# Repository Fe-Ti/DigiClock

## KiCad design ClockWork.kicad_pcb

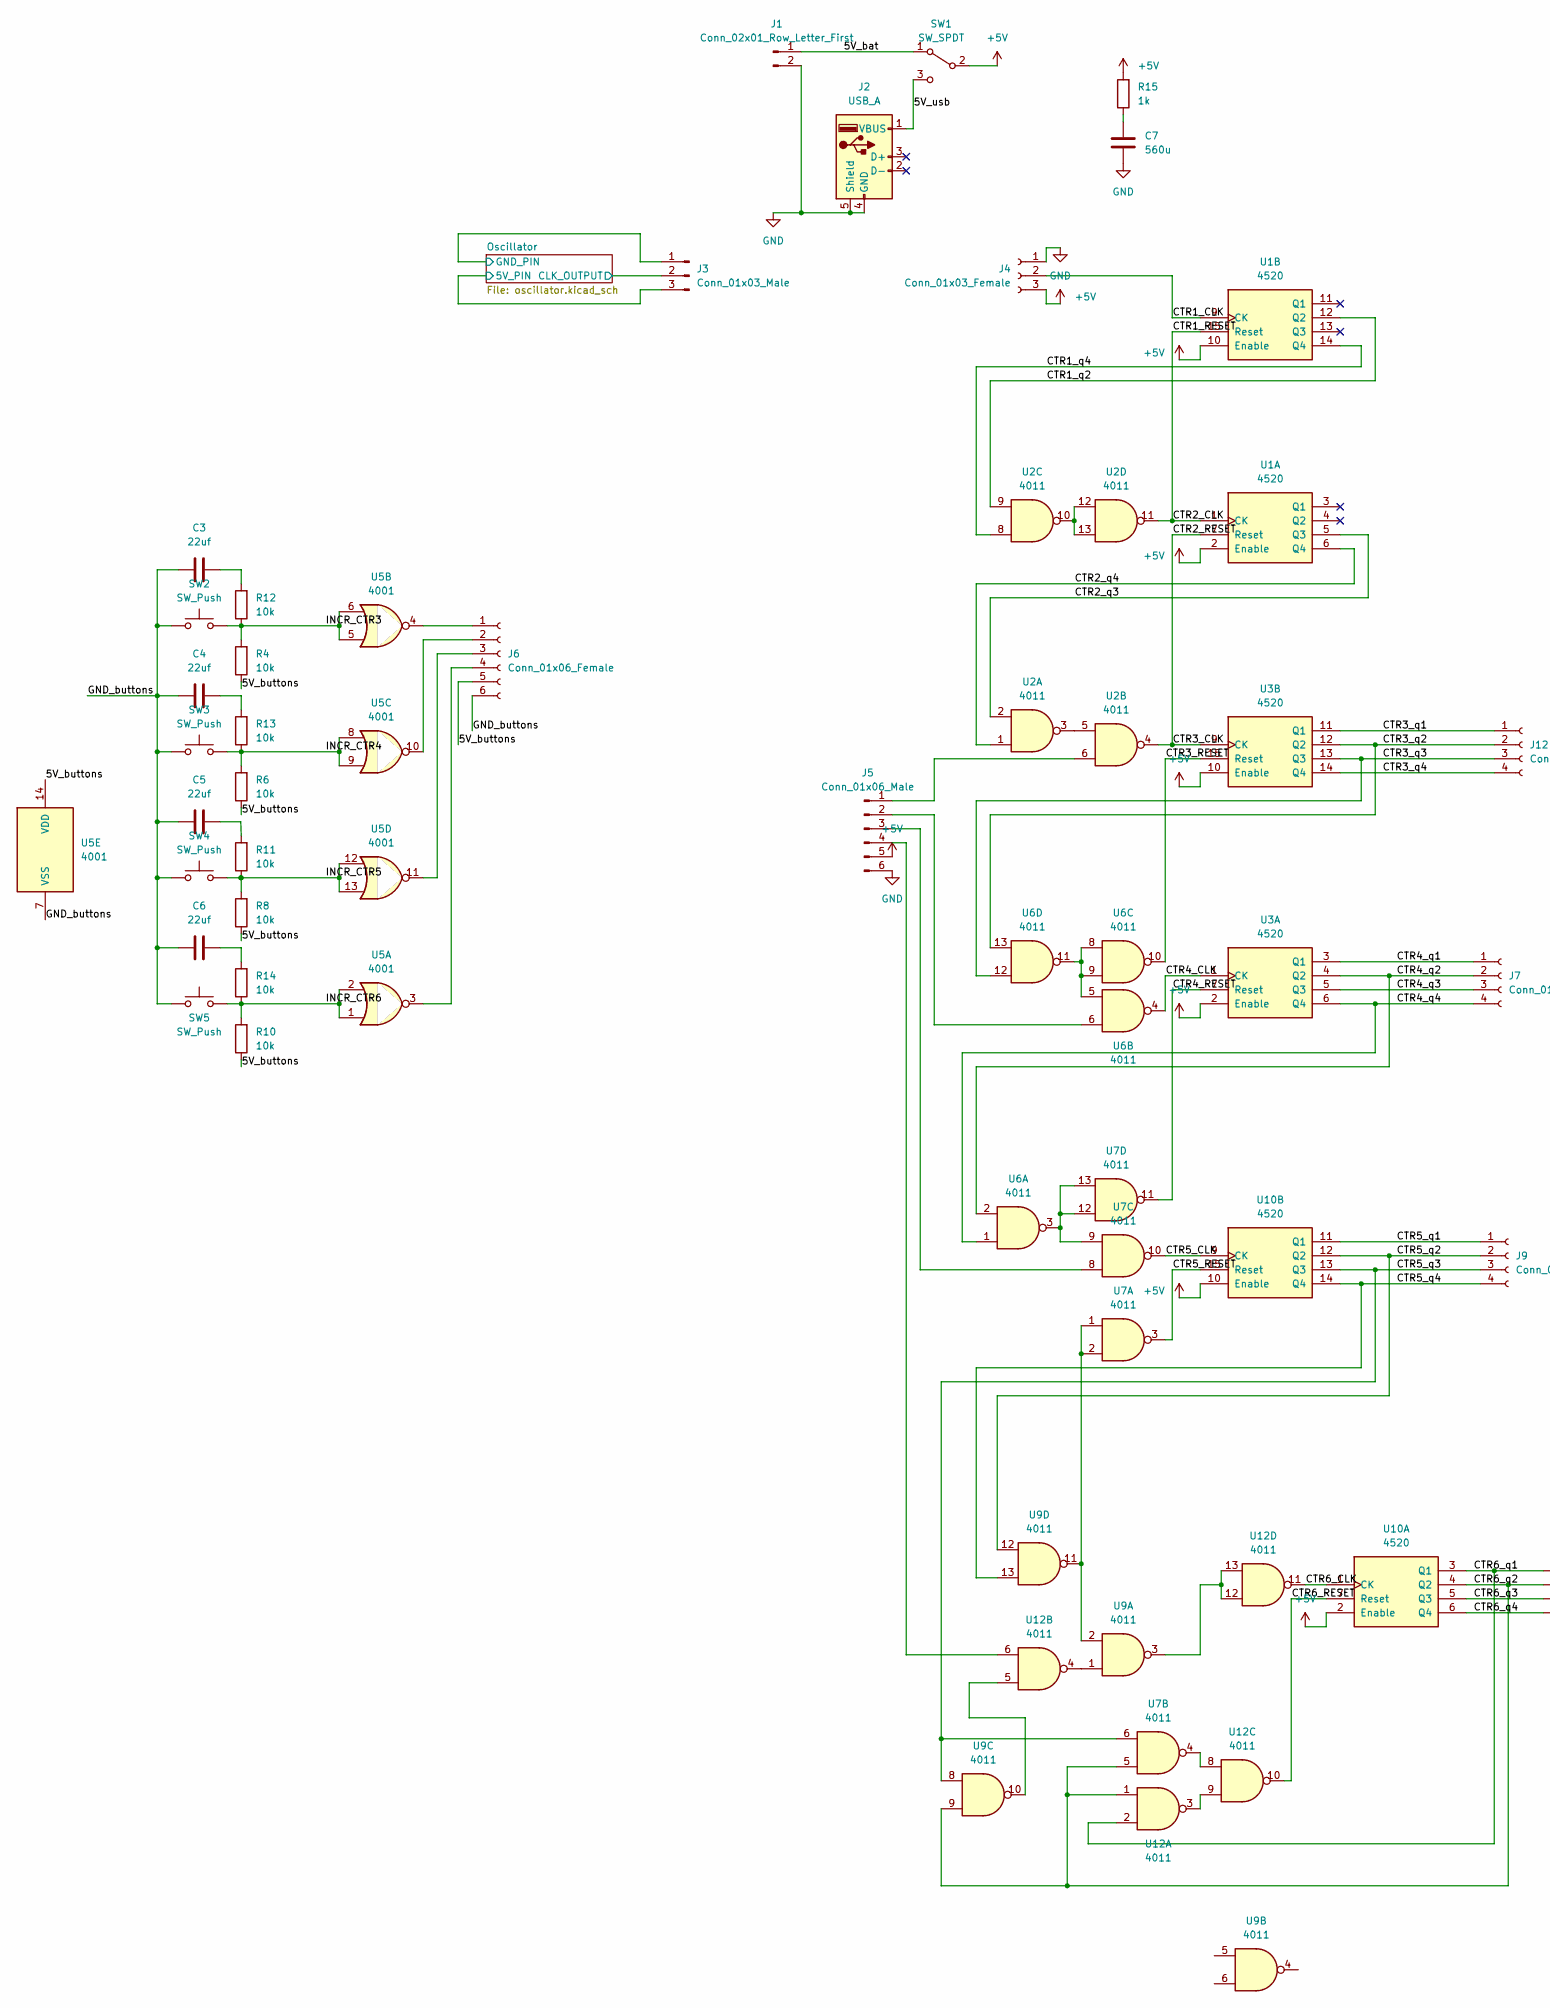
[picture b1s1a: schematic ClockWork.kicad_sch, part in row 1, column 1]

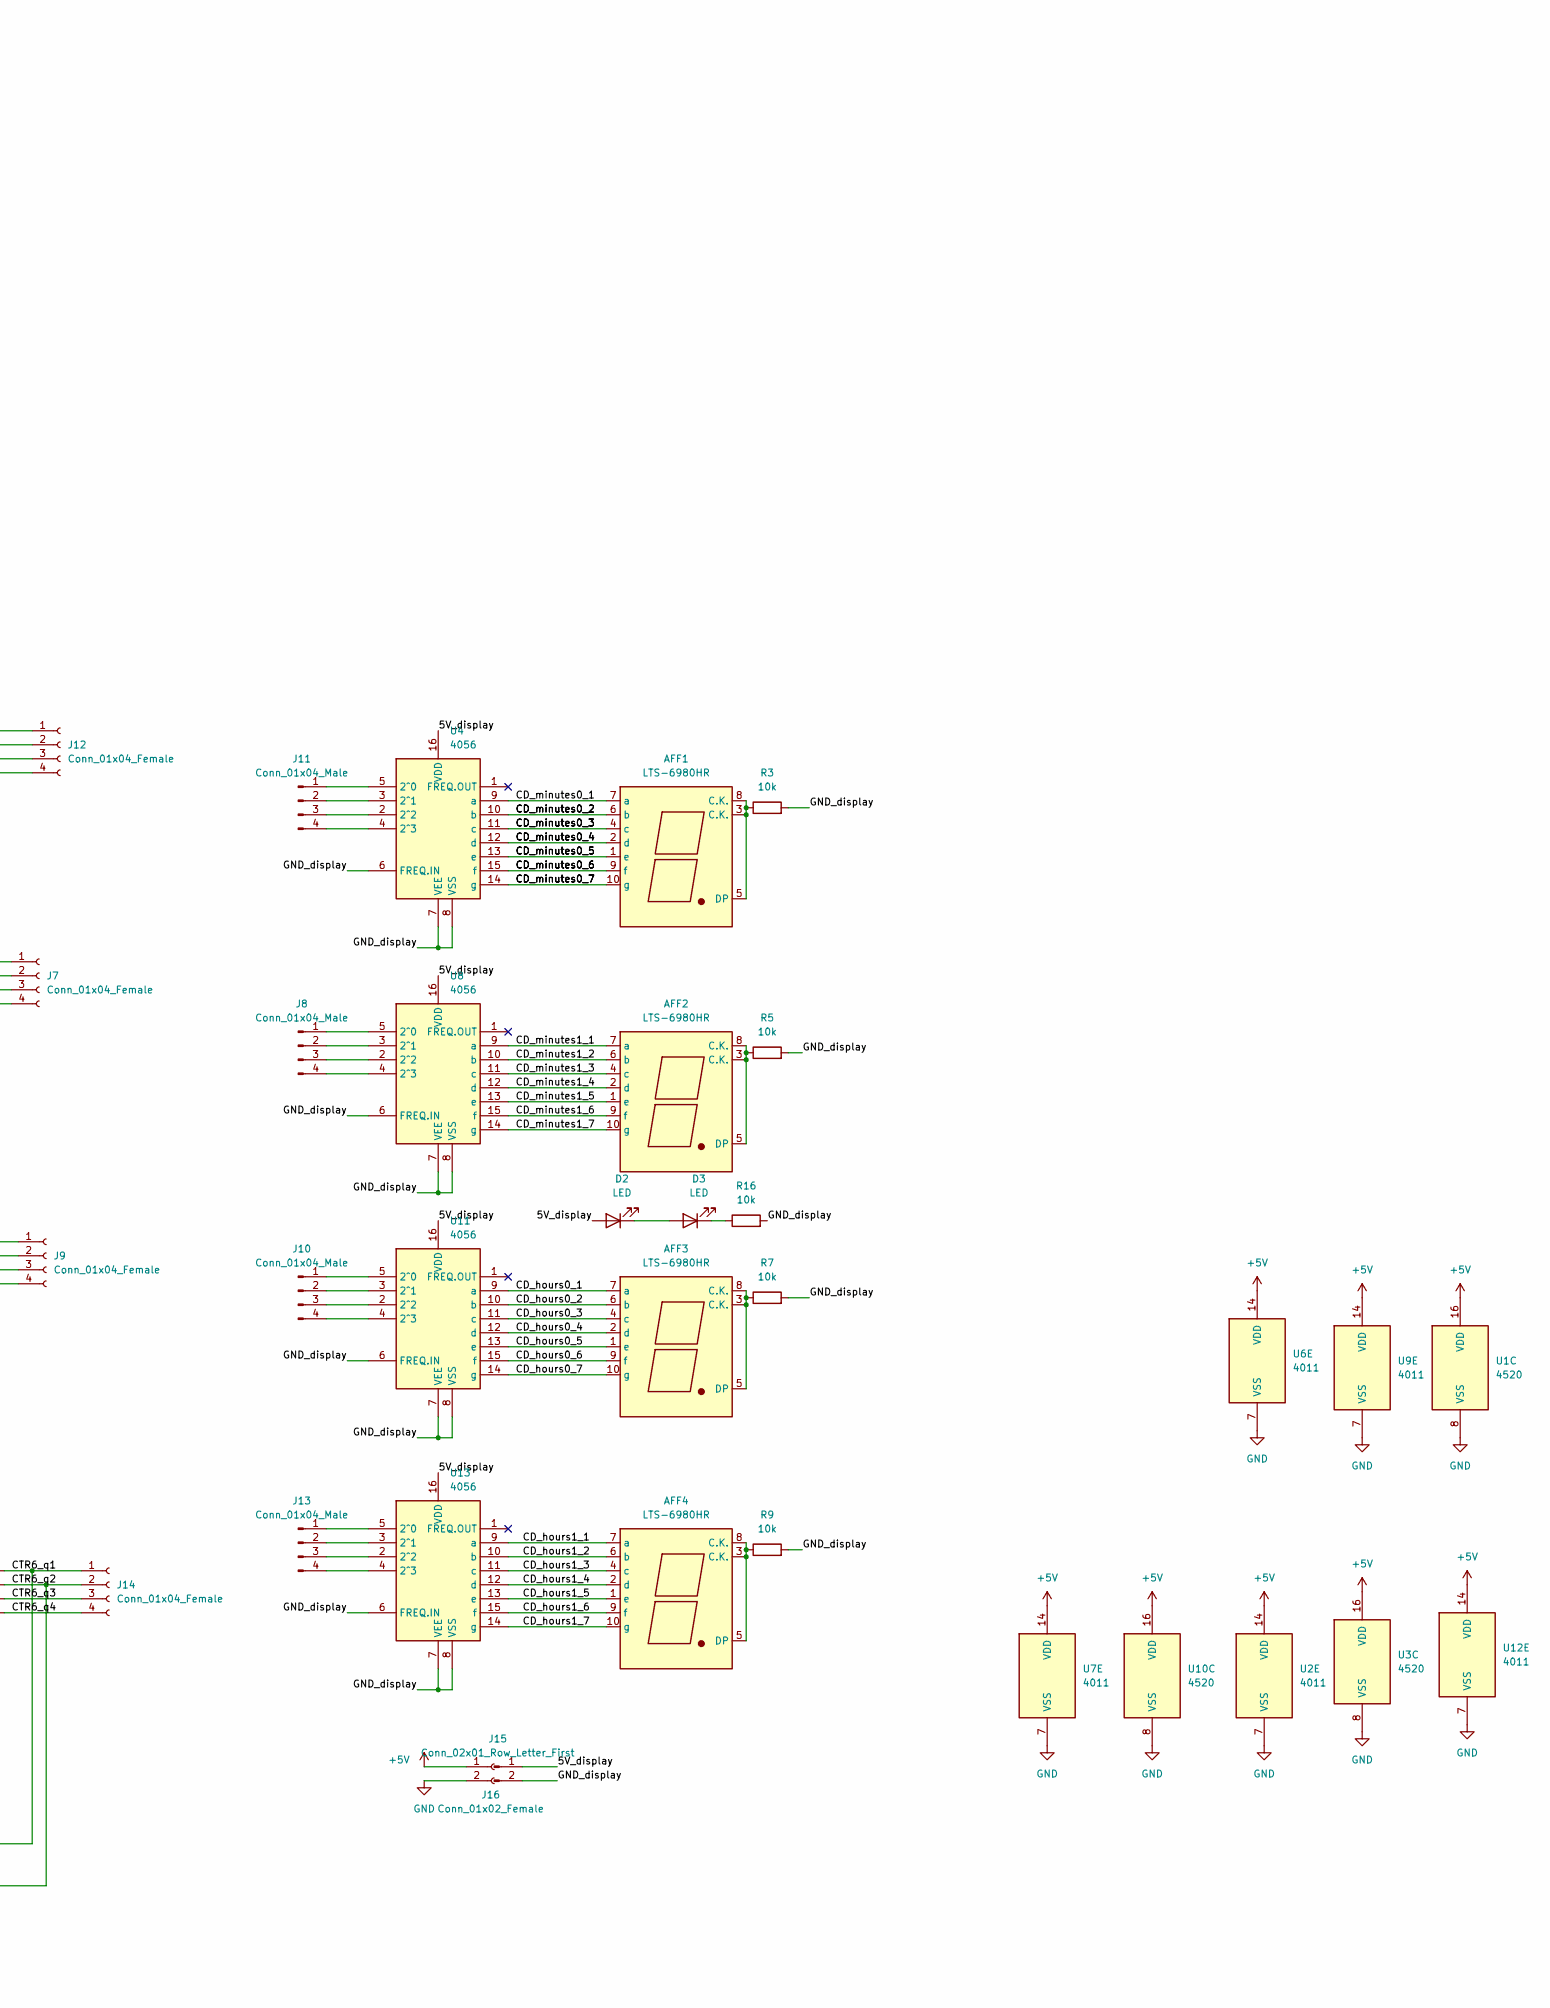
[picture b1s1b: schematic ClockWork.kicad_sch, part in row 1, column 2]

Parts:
AFF1, AFF2, AFF3, AFF4: LTS-6980HR; 7SegmentLED_LTS6760_LTS6780
C3, C4, C5, C6: 22uf; CP_Axial_L10.0mm_D4.5mm_P15.00mm_Horizontal
C7: 560u; CP_Radial_D10.0mm_P5.00mm
D2, D3: LED; LED_D5.0mm
J1: Conn_02x01_Row_Letter_First; PinHeader_1x02_P2.54mm_Vertical
J2: USB_A; USB_A_CONNFLY_DS1095-WNR0
J3: Conn_01x03_Male; PinHeader_1x03_P2.54mm_Vertical
J4: Conn_01x03_Female; PinSocket_1x03_P2.54mm_Vertical
J5: Conn_01x06_Male; PinSocket_1x06_P2.54mm_Vertical
J6: Conn_01x06_Female; PinSocket_1x06_P2.54mm_Vertical
J7, J9, J12, J14: Conn_01x04_Female; PinSocket_1x04_P2.54mm_Vertical
J8, J10, J11, J13: Conn_01x04_Male; PinSocket_1x04_P2.54mm_Vertical
J15: Conn_02x01_Row_Letter_First; PinSocket_1x02_P2.54mm_Vertical
J16: Conn_01x02_Female; PinSocket_1x02_P2.54mm_Vertical
R3, R4, R5, R6, R7, R8, R9, R10, R11, R12, R13, R14, R16: 10k; R_Axial_DIN0207_L6.3mm_D2.5mm_P7.62mm_Horizontal
R15: 1k; R_Axial_DIN0207_L6.3mm_D2.5mm_P7.62mm_Horizontal
SW1: SW_SPDT; PinSocket_1x03_P2.54mm_Vertical
SW2, SW3, SW4, SW5: SW_Push; SW_SPST_B3S-1000
U1, U3, U10: 4520; DIP-16_W7.62mm_Socket
U2, U6, U7, U9, U12: 4011; DIP-14_W7.62mm_Socket
U4, U8, U11, U13: 4056; DIP-16_W7.62mm_Socket
U5: 4001; DIP-14_W7.62mm_Socket

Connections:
+5V: J4.3, J5.5, J16.1, R15.2, SW1.2 (B), U1.2 (Enable), U1.10 (Enable), U1.16 (VDD), U2.14 (VDD), U3.2 (Enable), U3.10 (Enable), U3.16 (VDD), U6.14 (VDD), U7.14 (VDD), U9.14 (VDD), U10.2 (Enable), U10.10 (Enable), U10.16 (VDD), U12.14 (VDD)
/5V_bat: J1.1, SW1.1 (A)
/5V_buttons: J6.5, R4.1, R6.1, R8.1, R10.1, U5.14 (VDD)
/5V_display: D2.2 (A), J15.1, U4.16 (VDD), U8.16 (VDD), U11.16 (VDD), U13.16 (VDD)
/5V_usb: J2.1 (VBUS), SW1.3 (C)
/CD_hours0_1: AFF3.7 (a), U11.9 (a)
/CD_hours0_2: AFF3.6 (b), U11.10 (b)
/CD_hours0_3: AFF3.4 (c), U11.11 (c)
/CD_hours0_4: AFF3.2 (d), U11.12 (d)
/CD_hours0_5: AFF3.1 (e), U11.13 (e)
/CD_hours0_6: AFF3.9 (f), U11.15 (f)
/CD_hours0_7: AFF3.10 (g), U11.14 (g)
/CD_hours1_1: AFF4.7 (a), U13.9 (a)
/CD_hours1_2: AFF4.6 (b), U13.10 (b)
/CD_hours1_3: AFF4.4 (c), U13.11 (c)
/CD_hours1_4: AFF4.2 (d), U13.12 (d)
/CD_hours1_5: AFF4.1 (e), U13.13 (e)
/CD_hours1_6: AFF4.9 (f), U13.15 (f)
/CD_hours1_7: AFF4.10 (g), U13.14 (g)
/CD_minutes0_1: AFF1.7 (a), U4.9 (a)
/CD_minutes0_2: AFF1.6 (b), U4.10 (b)
/CD_minutes0_4: AFF1.2 (d), U4.12 (d)
/CD_minutes0_5: AFF1.1 (e), U4.13 (e)
/CD_minutes0_6: AFF1.9 (f), U4.15 (f)
/CD_minutes0_7: AFF1.10 (g), U4.14 (g)
/CD_minutes1_1: AFF2.7 (a), U8.9 (a)
/CD_minutes1_2: AFF2.6 (b), U8.10 (b)
/CD_minutes1_3: AFF2.4 (c), U8.11 (c)
/CD_minutes1_4: AFF2.2 (d), U8.12 (d)
/CD_minutes1_5: AFF2.1 (e), U8.13 (e)
/CD_minutes1_6: AFF2.9 (f), U8.15 (f)
/CD_minutes1_7: AFF2.10 (g), U8.14 (g)
/CTR1_CLK: J4.2, U1.9 (CK)
/CTR1_RESET: U1.1 (CK), U1.15 (Reset), U2.11
/CTR1_q2: U1.12 (Q2), U2.9
/CTR1_q4: U1.14 (Q4), U2.8
/CTR2_RESET: U1.7 (Reset), U2.4, U3.9 (CK)
/CTR2_q3: U1.5 (Q3), U2.2
/CTR2_q4: U1.6 (Q4), U2.1
/CTR3_RESET: U3.15 (Reset), U6.10
/CTR3_q1: J12.1, U3.11 (Q1)
/CTR3_q2: J12.2, U3.12 (Q2), U6.13
/CTR3_q3: J12.3, U3.13 (Q3), U6.12
/CTR3_q4: J12.4, U3.14 (Q4)
/CTR4_CLK: U3.1 (CK), U6.4
/CTR4_RESET: U3.7 (Reset), U7.11
/CTR4_q1: J7.1, U3.3 (Q1)
/CTR4_q2: J7.2, U3.4 (Q2), U6.2
/CTR4_q3: J7.3, U3.5 (Q3)
/CTR4_q4: J7.4, U3.6 (Q4), U6.1
/CTR5_CLK: U7.10, U10.9 (CK)
/CTR5_RESET: U7.3, U10.15 (Reset)
/CTR5_q1: J9.1, U10.11 (Q1)
/CTR5_q2: J9.2, U9.12, U10.12 (Q2)
/CTR5_q3: J9.3, U7.6, U9.8, U10.13 (Q3)
/CTR5_q4: J9.4, U9.13, U10.14 (Q4)
/CTR6_CLK: U10.1 (CK), U12.11
/CTR6_RESET: U10.7 (Reset), U12.10
/CTR6_q1: J14.1, U10.3 (Q1), U12.2
/CTR6_q2: J14.2, U7.5, U9.9, U10.4 (Q2), U12.1
/CTR6_q3: J14.3, U10.5 (Q3)
/CTR6_q4: J14.4, U10.6 (Q4)
/GND_buttons: C3.1, C4.1, C5.1, C6.1, J6.6, SW2.1, SW3.1, SW4.1, SW5.1, U5.7 (VSS)
/GND_display: J15.2, R3.2, R5.2, R7.2, R9.2, R16.2, U4.6 (FREQ.IN), U4.7 (VEE), U4.8 (VSS), U8.6 (FREQ.IN), U8.7 (VEE), U8.8 (VSS), U11.6 (FREQ.IN), U11.7 (VEE), U11.8 (VSS), U13.6 (FREQ.IN), U13.7 (VEE), U13.8 (VSS)
/INCR_CTR3: R4.2, R12.1, SW2.2, U5.5, U5.6
/INCR_CTR4: R6.2, R13.1, SW3.2, U5.8, U5.9
/INCR_CTR5: R8.2, R11.1, SW4.2, U5.12, U5.13
/INCR_CTR6: R10.2, R14.1, SW5.2, U5.1, U5.2
/Oscillator/5V: J3.3; also elsewhere on the board
/Oscillator/CLK_OUTPUT: J3.2; also elsewhere on the board
/Oscillator/GND: J3.1; also elsewhere on the board
GND: C7.2, J1.2, J2.4 (GND), J2.5 (Shield), J4.1, J5.6, J16.2, U1.8 (VSS), U2.7 (VSS), U3.8 (VSS), U6.7 (VSS), U7.7 (VSS), U9.7 (VSS), U10.8 (VSS), U12.7 (VSS)
unnamed: AFF1.3 (C.K.), AFF1.5 (DP), AFF1.8 (C.K.), R3.1
unnamed: AFF1.4 (c), U4.11 (c)
unnamed: AFF2.3 (C.K.), AFF2.5 (DP), AFF2.8 (C.K.), R5.1
unnamed: AFF3.3 (C.K.), AFF3.5 (DP), AFF3.8 (C.K.), R7.1
unnamed: AFF4.3 (C.K.), AFF4.5 (DP), AFF4.8 (C.K.), R9.1
unnamed: C3.2, R12.2
unnamed: C4.2, R13.2
unnamed: C5.2, R11.2
unnamed: C6.2, R14.2
unnamed: C7.1, R15.1
unnamed: D2.1 (K), D3.2 (A)
unnamed: D3.1 (K), R16.1
unnamed: J5.1, U2.6
unnamed: J5.2, U6.6
unnamed: J5.3, U7.8
unnamed: J5.4, U12.6
unnamed: J6.1, U5.4
unnamed: J6.2, U5.10
unnamed: J6.3, U5.11
unnamed: J6.4, U5.3
unnamed: J8.1, U8.5 (2^0)
unnamed: J8.2, U8.3 (2^1)
unnamed: J8.3, U8.2 (2^2)
unnamed: J8.4, U8.4 (2^3)
unnamed: J10.1, U11.5 (2^0)
unnamed: J10.2, U11.3 (2^1)
unnamed: J10.3, U11.2 (2^2)
unnamed: J10.4, U11.4 (2^3)
unnamed: J11.1, U4.5 (2^0)
unnamed: J11.2, U4.3 (2^1)
unnamed: J11.3, U4.2 (2^2)
unnamed: J11.4, U4.4 (2^3)
unnamed: J13.1, U13.5 (2^0)
unnamed: J13.2, U13.3 (2^1)
unnamed: J13.3, U13.2 (2^2)
unnamed: J13.4, U13.4 (2^3)
unnamed: U2.3, U2.5
unnamed: U2.10, U2.12, U2.13
unnamed: U6.3, U7.9, U7.12, U7.13
unnamed: U6.5, U6.8, U6.9, U6.11
unnamed: U7.1, U7.2, U9.2, U9.11
unnamed: U12.3, U12.9
unnamed: U9.1, U12.4
unnamed: U9.10, U12.5
unnamed: U7.4, U12.8
unnamed: U9.3, U12.12, U12.13

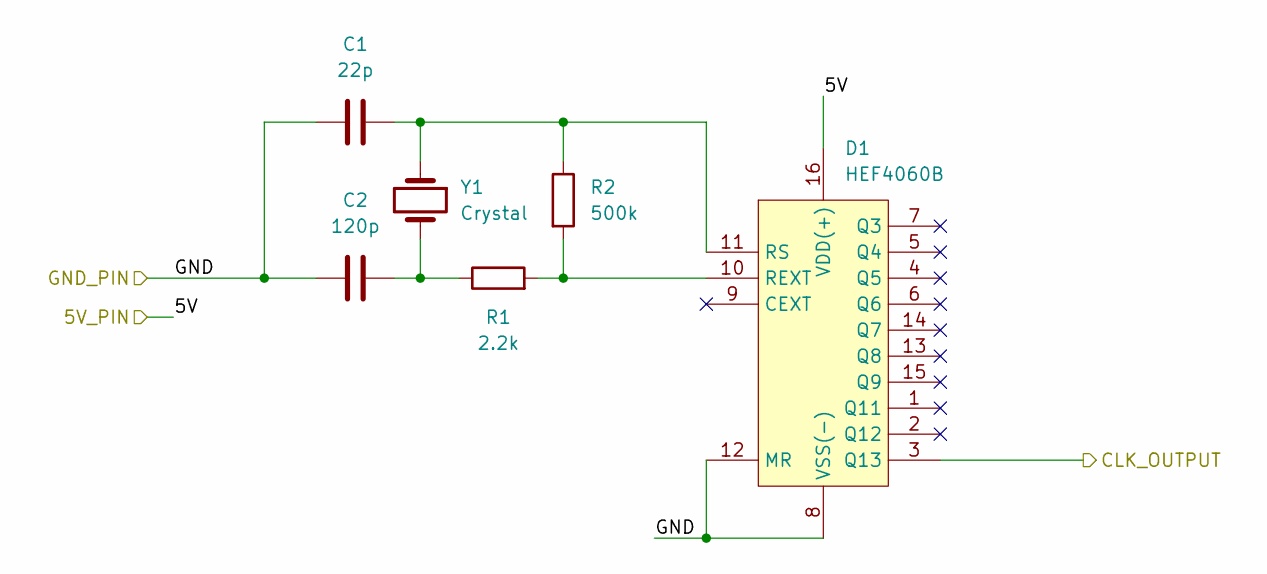
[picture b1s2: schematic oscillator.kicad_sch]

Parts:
C1: 22p; C_Trimmer_Murata_TZC3
C2: 120p; C_Disc_D8.0mm_W2.5mm_P5.00mm
D1: HEF4060B; SO-16_3.9x9.9mm_P1.27mm
R1: 2.2k; R_Axial_DIN0309_L9.0mm_D3.2mm_P2.54mm_Vertical
R2: 500k; R_Axial_DIN0309_L9.0mm_D3.2mm_P2.54mm_Vertical
Y1: Crystal; Crystal_C38-LF_D3.0mm_L8.0mm_Vertical

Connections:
/Oscillator/5V: D1.16 (VDD(+)); also elsewhere on the board
/Oscillator/CLK_OUTPUT: D1.3 (Q13); also elsewhere on the board
/Oscillator/GND: C1.1, C2.1, D1.8 (VSS(-)), D1.12 (MR); also elsewhere on the board
unnamed: C1.2, D1.11 (RS), R2.1, Y1.1
unnamed: C2.2, R1.1, Y1.2
unnamed: D1.10 (REXT), R1.2, R2.2

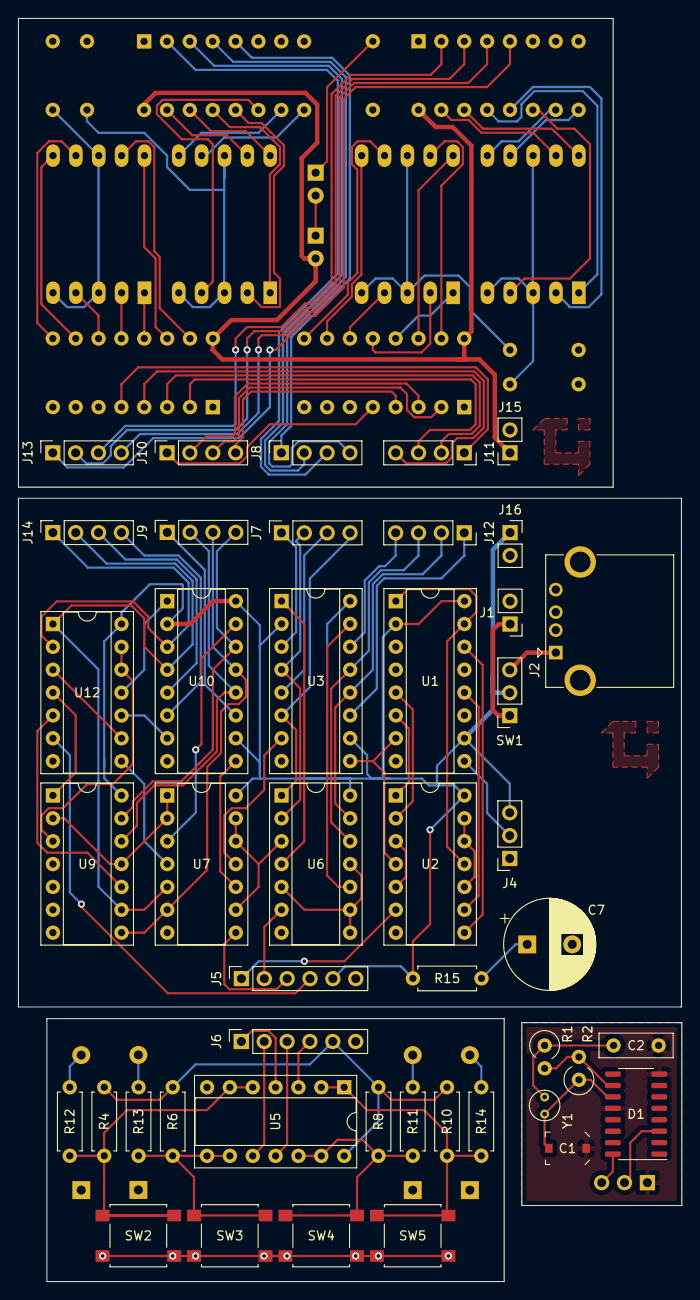
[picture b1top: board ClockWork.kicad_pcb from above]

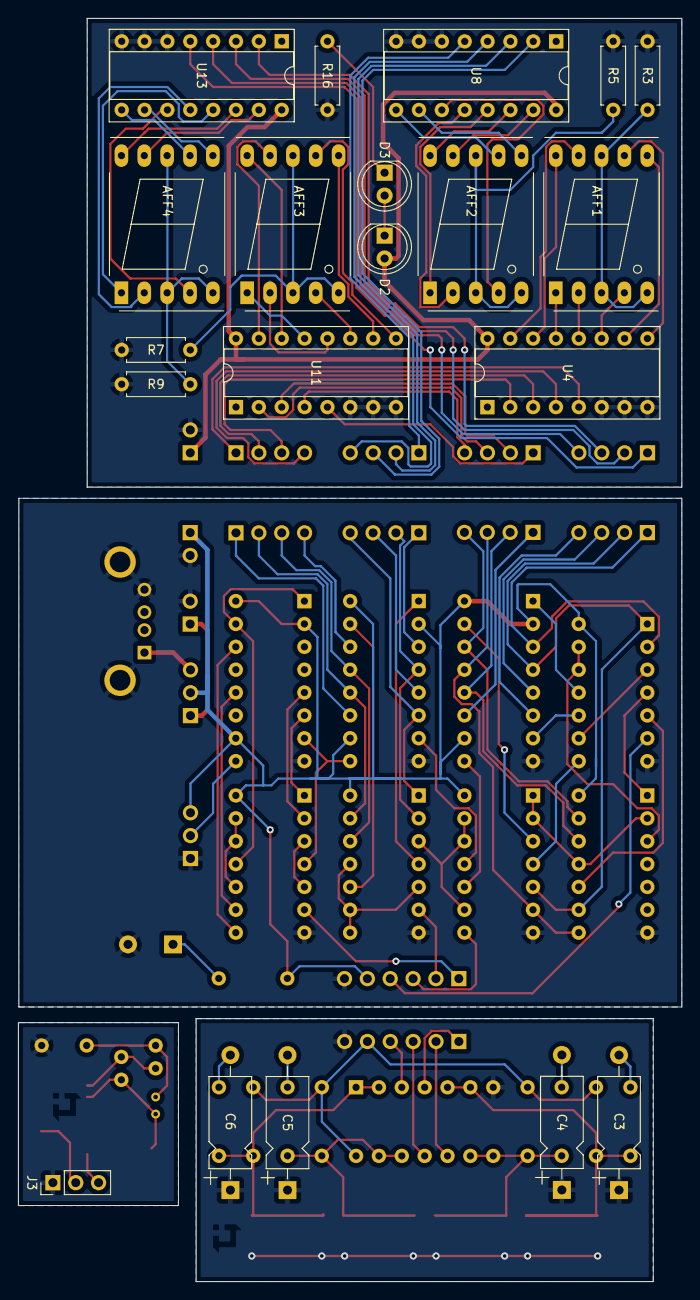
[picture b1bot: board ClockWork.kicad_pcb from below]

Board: 2 copper layers, 73.7 x 140.3 mm, 65 parts (20 on the bottom side), 121 nets.

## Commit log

2023-02-06 Initial commit. Finished first clock PCB.
2023-02-06 Minor changes in design
